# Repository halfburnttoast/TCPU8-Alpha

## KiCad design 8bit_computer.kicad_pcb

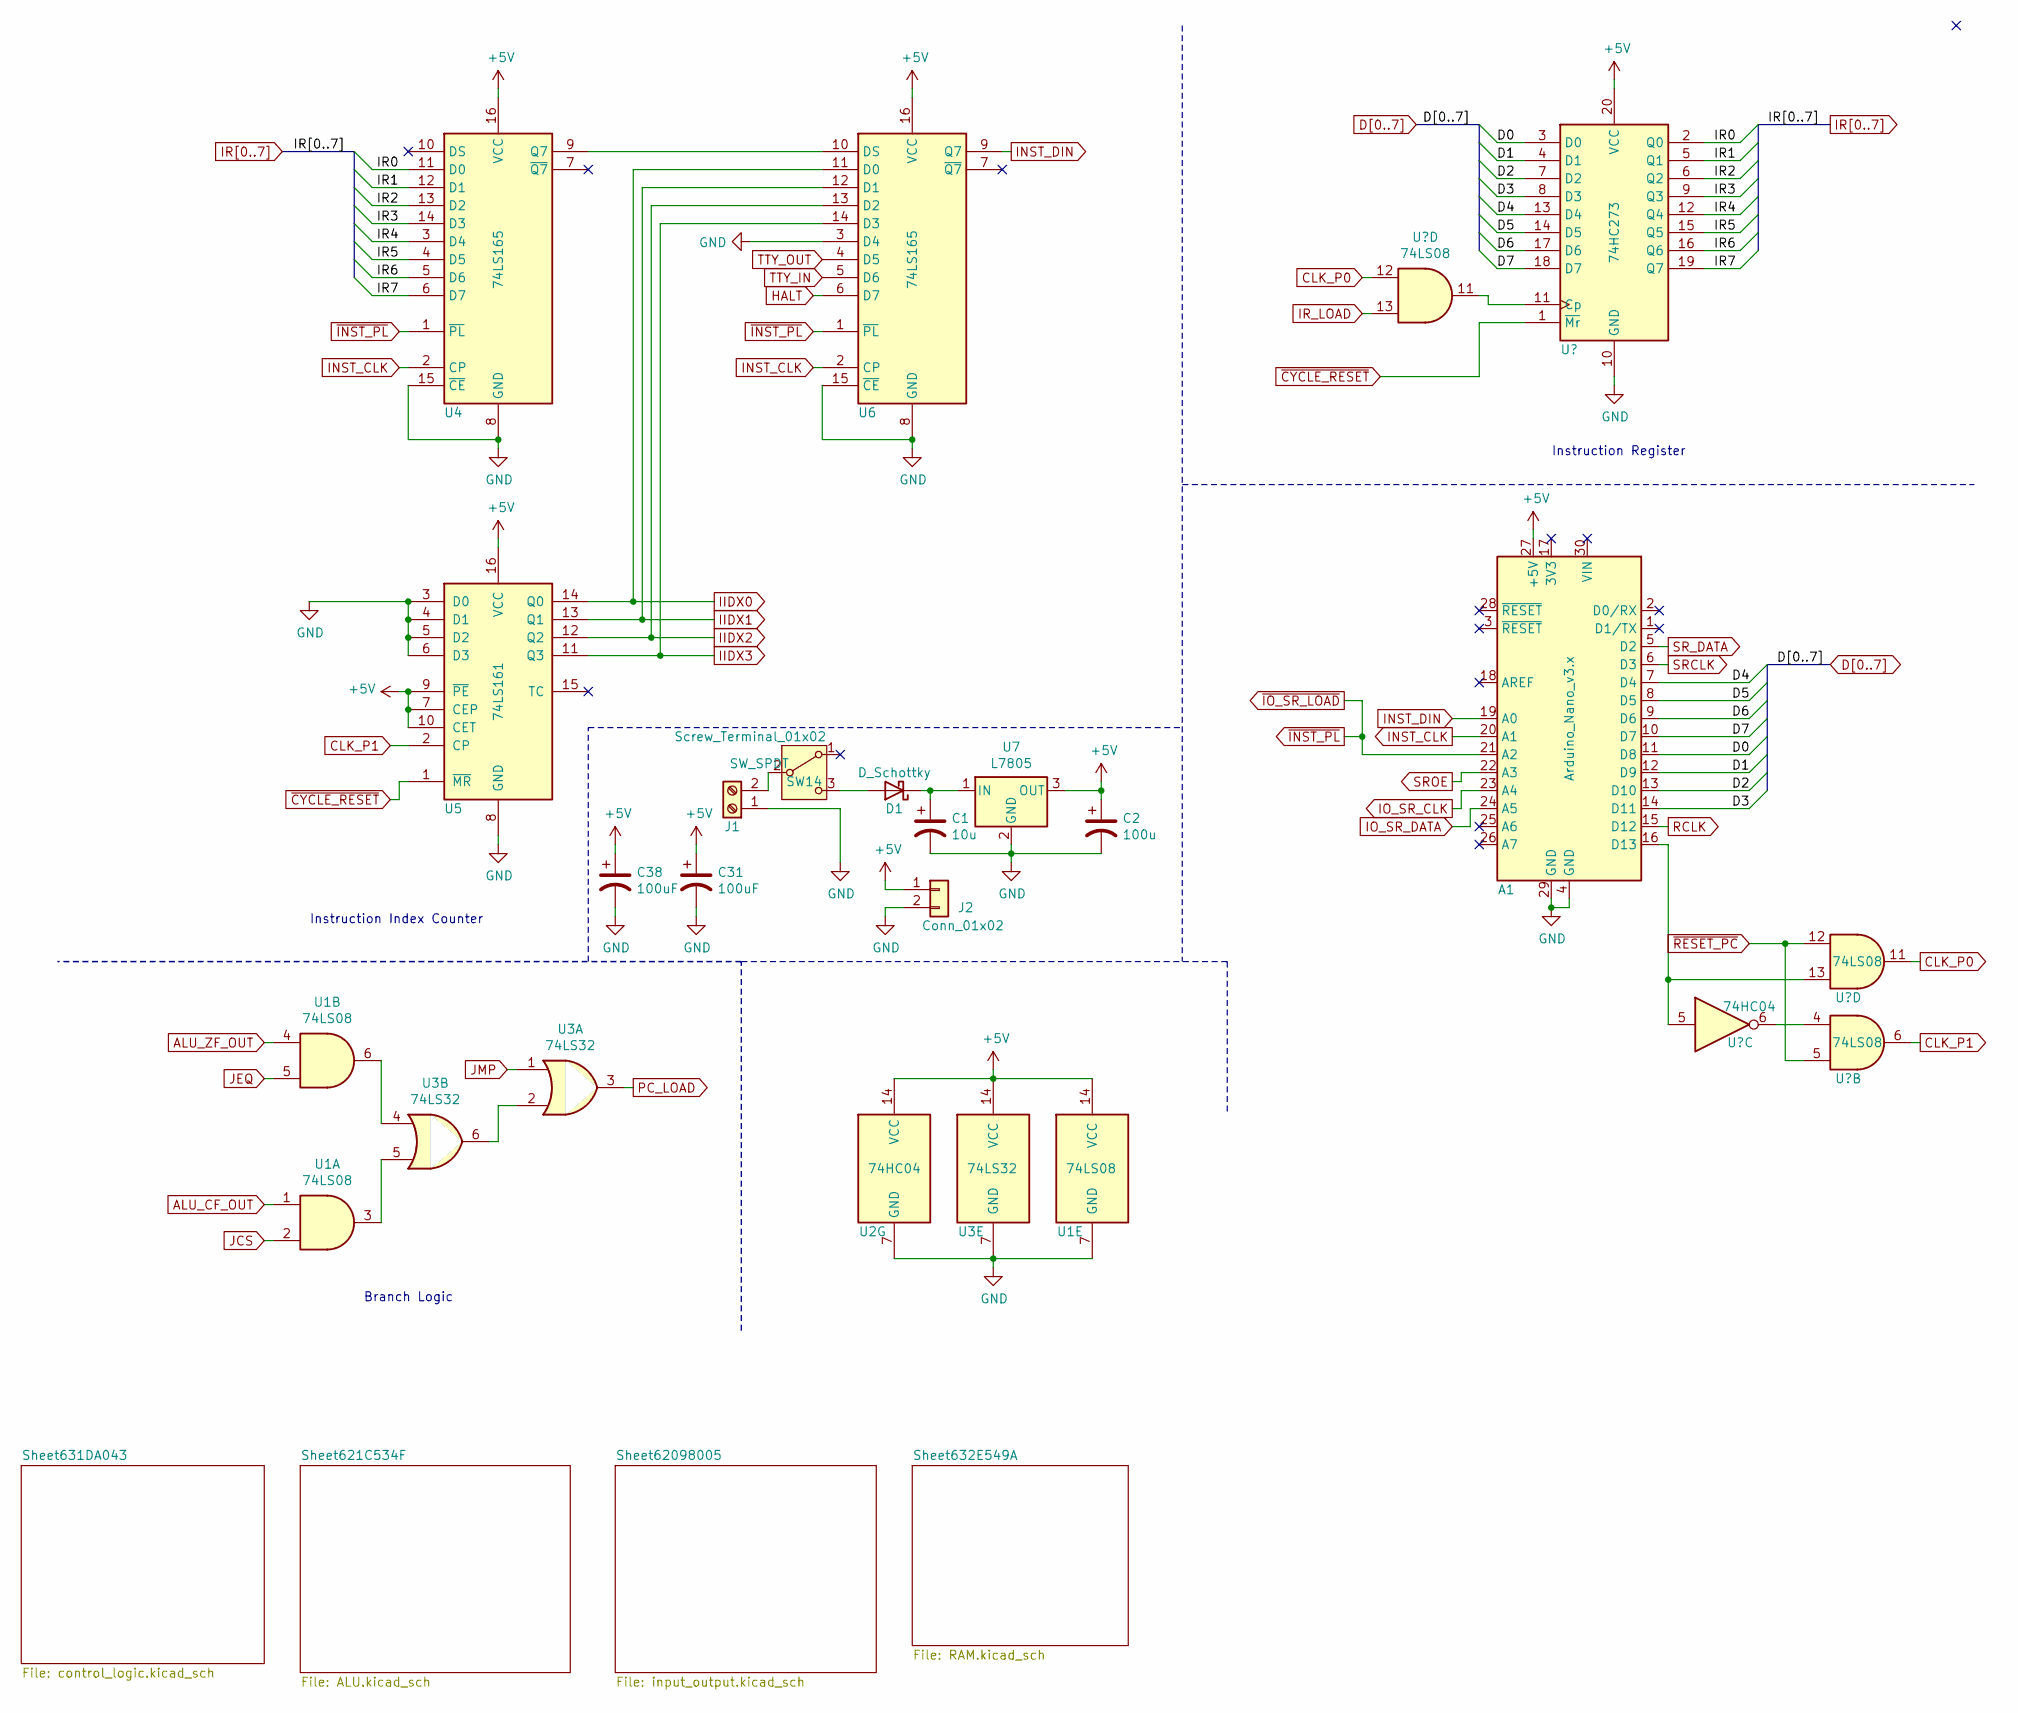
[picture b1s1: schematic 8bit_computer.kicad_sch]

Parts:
A1: Arduino_Nano_v3.x; Arduino_Nano
C1: 10u; CP_Radial_D4.0mm_P2.00mm
C2: 100u; CP_Radial_D4.0mm_P2.00mm
C31, C38: 100uF; CP_Radial_D4.0mm_P2.00mm
D1: D_Schottky; D_SOD-123
J1: Screw_Terminal_01x02; TerminalBlock_bornier-2_P5.08mm
J2: Conn_01x02; PinSocket_1x02_P2.54mm_Vertical
SW14: SW_SPDT; spdt_slide_switch
U1, U10: 74LS08; DIP-14_W7.62mm
U2: 74HC04; DIP-14_W7.62mm
U3: 74LS32; DIP-14_W7.62mm
U4, U6: 74LS165; DIP-16_W7.62mm
U5: 74LS161; DIP-16_W7.62mm
U7: L7805; TO-220F-3_Horizontal_TabDown
U8: 74HC273; DIP-20_W7.62mm

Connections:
+5V: A1.27 (+5V), C2.1, C31.1, C38.1, J2.1, U1.14 (VCC), U2.14 (VCC), U3.14 (VCC), U4.16 (VCC), U5.7 (CEP), U5.9 (~PE), U5.10 (CET), U5.16 (VCC), U6.16 (VCC), U7.3 (OUT), U8.20 (VCC); also elsewhere on the board
ALU_CF_OUT: U1.1; also elsewhere on the board
ALU_ZF_OUT: U1.4; also elsewhere on the board
CLK_P0: U1.12, U10.11; also elsewhere on the board
CLK_P1: U5.2 (CP), U10.6; also elsewhere on the board
D0: A1.11 (D8), U8.3 (D0); also elsewhere on the board
D1: A1.12 (D9), U8.4 (D1); also elsewhere on the board
D2: A1.13 (D10), U8.7 (D2); also elsewhere on the board
D3: A1.14 (D11), U8.8 (D3); also elsewhere on the board
D4: A1.7 (D4), U8.13 (D4); also elsewhere on the board
D5: A1.8 (D5), U8.14 (D5); also elsewhere on the board
D6: A1.9 (D6), U8.17 (D6); also elsewhere on the board
D7: A1.10 (D7), U8.18 (D7); also elsewhere on the board
GND: A1.4 (GND), A1.29 (GND), C1.2, C2.2, C31.2, C38.2, J1.1, J2.2, U1.7 (GND), U2.7 (GND), U3.7 (GND), U4.8 (GND), U4.15 (~CE), U5.3 (D0), U5.4 (D1), U5.5 (D2), U5.6 (D3), U5.8 (GND), U6.3 (D4), U6.8 (GND), U6.15 (~CE), U7.2 (GND), U8.10 (GND); also elsewhere on the board
HALT: U6.6 (D7); also elsewhere on the board
IIDX0: U5.14 (Q0), U6.11 (D0); also elsewhere on the board
IIDX1: U5.13 (Q1), U6.12 (D1); also elsewhere on the board
IIDX2: U5.12 (Q2), U6.13 (D2); also elsewhere on the board
IIDX3: U5.11 (Q3), U6.14 (D3); also elsewhere on the board
INST_CLK: A1.20 (A1), U4.2 (CP), U6.2 (CP)
INST_DIN: A1.19 (A0), U6.9 (Q7)
IO_SR_CLK: A1.23 (A4); also elsewhere on the board
IO_SR_DATA: A1.24 (A5); also elsewhere on the board
IR0: U4.11 (D0), U8.2 (Q0); also elsewhere on the board
IR1: U4.12 (D1), U8.5 (Q1); also elsewhere on the board
IR2: U4.13 (D2), U8.6 (Q2); also elsewhere on the board
IR3: U4.14 (D3), U8.9 (Q3); also elsewhere on the board
IR4: U4.3 (D4), U8.12 (Q4); also elsewhere on the board
IR5: U4.4 (D5), U8.15 (Q5); also elsewhere on the board
IR6: U4.5 (D6), U8.16 (Q6); also elsewhere on the board
IR7: U4.6 (D7), U8.19 (Q7); also elsewhere on the board
IR_LOAD: U1.13; also elsewhere on the board
JCS: U1.2; also elsewhere on the board
JEQ: U1.5; also elsewhere on the board
JMP: U3.1; also elsewhere on the board
unnamed: A1.16 (D13), U2.5, U10.13
unnamed: C1.1, D1.1 (K), U7.1 (IN)
unnamed: D1.2 (A), SW14.3 (C)
unnamed: J1.2, SW14.2 (B)
unnamed: U1.3, U3.5
unnamed: U1.6, U3.4
unnamed: U1.11, U8.11 (Cp)
unnamed: U3.2, U3.6
unnamed: U4.9 (Q7), U6.10 (DS)
unnamed: U2.6, U10.4
PC_LOAD: U3.3; also elsewhere on the board
RCLK: A1.15 (D12); also elsewhere on the board
SRCLK: A1.6 (D3); also elsewhere on the board
SROE: A1.22 (A3); also elsewhere on the board
SR_DATA: A1.5 (D2); also elsewhere on the board
TTY_IN: U6.5 (D6); also elsewhere on the board
TTY_OUT: U6.4 (D5); also elsewhere on the board
~CYCLE_RESET: U5.1 (~MR), U8.1 (~Mr); also elsewhere on the board
~INST_PL: A1.21 (A2), U4.1 (~PL), U6.1 (~PL); also elsewhere on the board
~RESET_PC: U10.5, U10.12; also elsewhere on the board

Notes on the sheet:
Instruction Register
Branch Logic
Instruction Index Counter

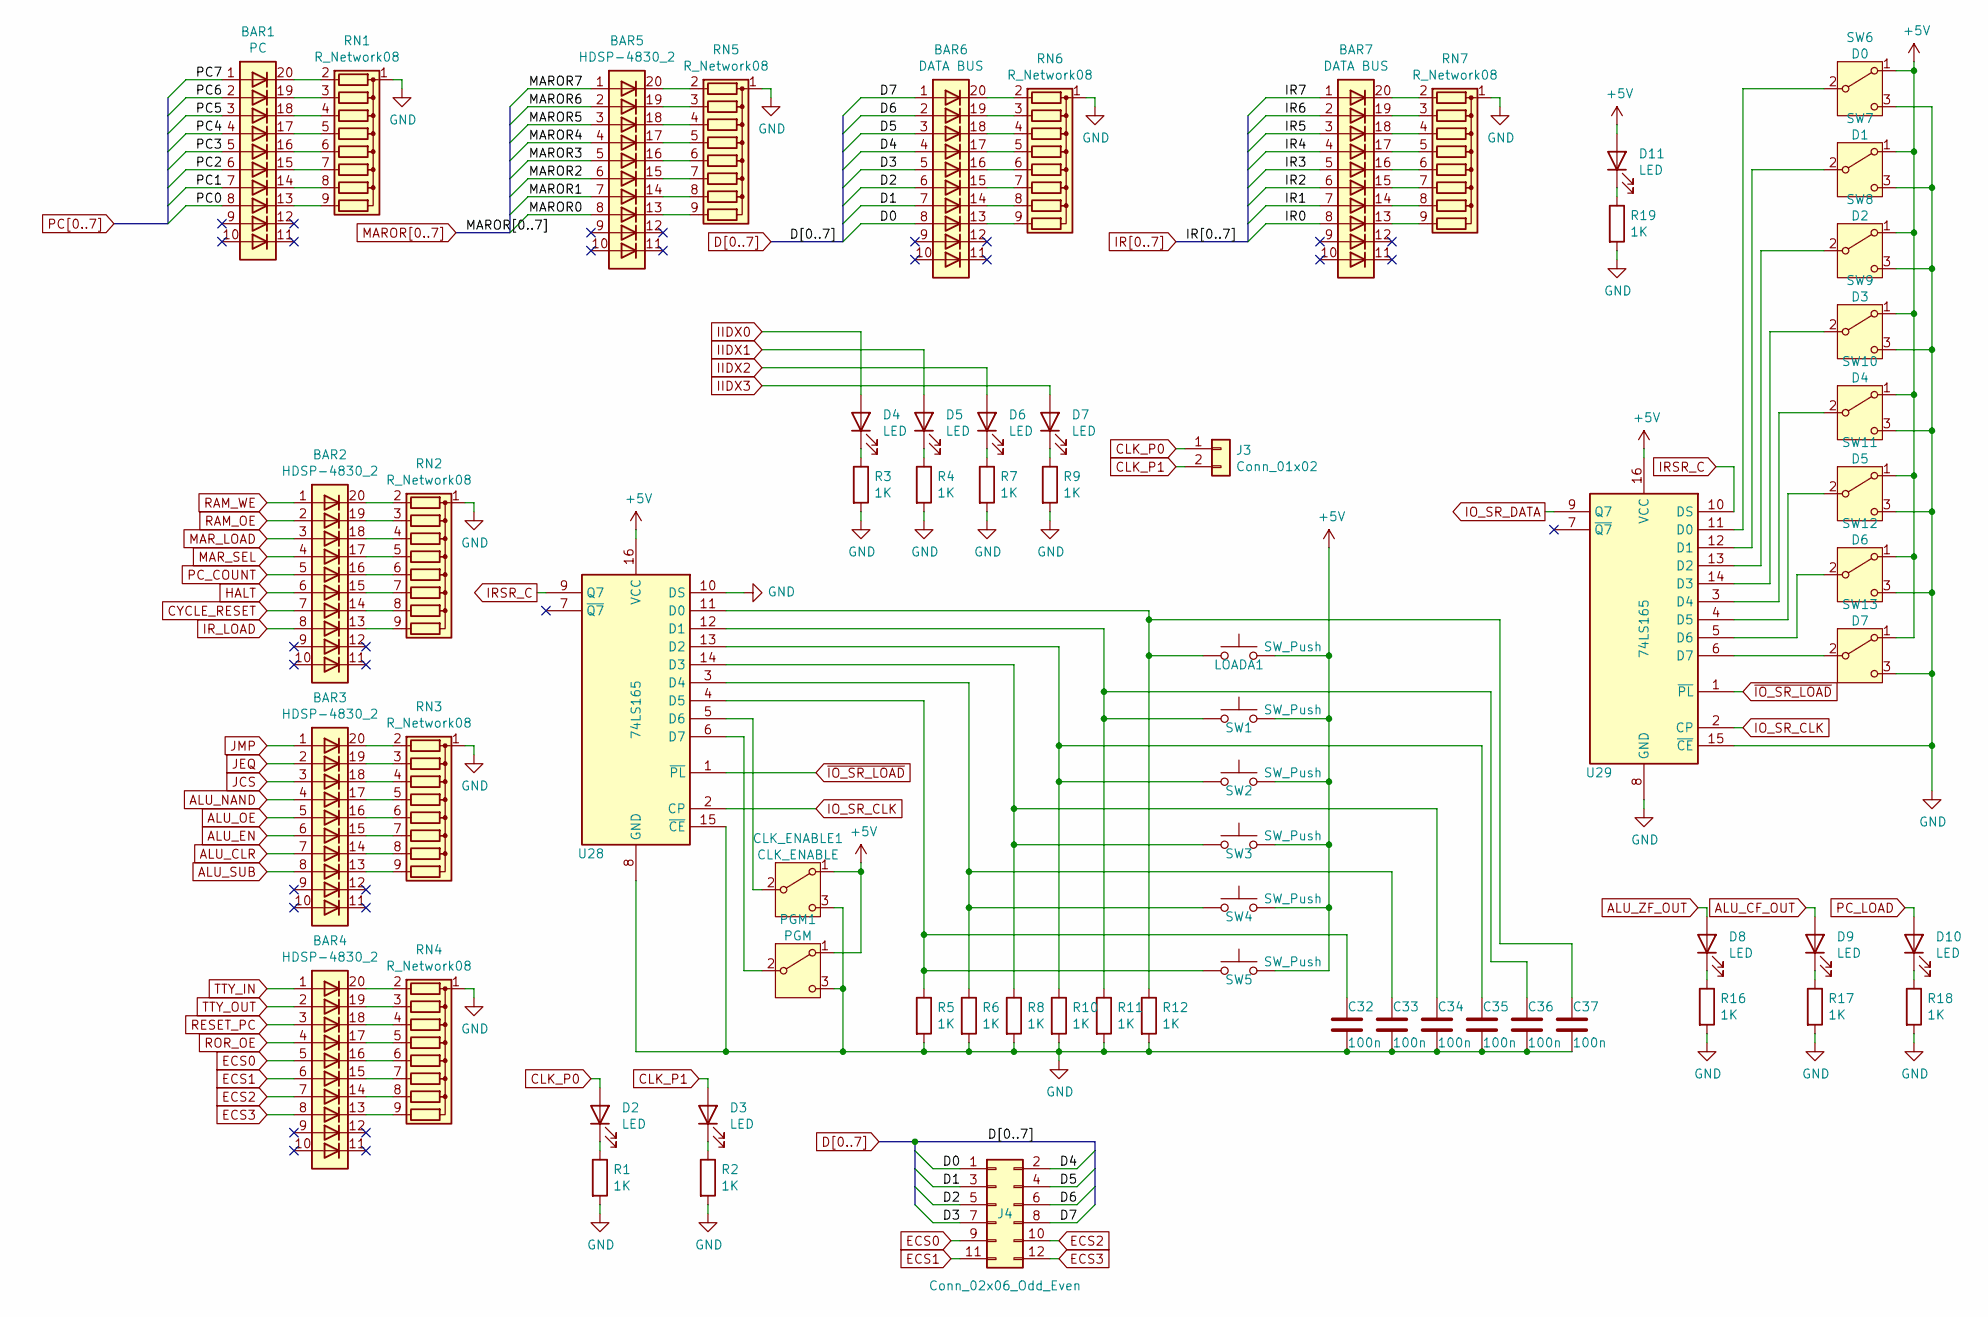
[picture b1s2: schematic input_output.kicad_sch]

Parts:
BAR1: PC; HDSP-4830
BAR2, BAR3, BAR4, BAR5: HDSP-4830_2; HDSP-4830
BAR6, BAR7: DATA BUS; HDSP-4830
C32, C33, C34, C35, C36, C37: 100n; C_1206_3216Metric_Pad1.42x1.75mm_HandSolder
CLK_ENABLE1: CLK_ENABLE; spdt_slide_switch
D2, D3: LED; LED_D5.0mm
D4, D5, D6, D7, D8, D9, D10, D11: LED; LED_D3.0mm
J3: Conn_01x02; PinSocket_1x02_P2.54mm_Vertical
J4: Conn_02x06_Odd_Even; PinSocket_2x06_P2.54mm_Vertical
LOADA1: SW_Push; SW_PUSH_6mm
PGM1: PGM; spdt_slide_switch
R1, R2, R3, R4, R5, R6, R7, R8, R9, R10, R11, R12, R19: 1K; R_Axial_DIN0207_L6.3mm_D2.5mm_P7.62mm_Horizontal
R16, R17, R18: 1K; R_1206_3216Metric_Pad1.42x1.75mm_HandSolder
RN1, RN2, RN3, RN4, RN5, RN6, RN7: R_Network08; R_Array_SIP9
SW1, SW2, SW3, SW4, SW5: SW_Push; SW_PUSH_6mm
SW6: D0; spdt_slide_switch
SW7: D1; spdt_slide_switch
SW8: D2; spdt_slide_switch
SW9: D3; spdt_slide_switch
SW10: D4; spdt_slide_switch
SW11: D5; spdt_slide_switch
SW12: D6; spdt_slide_switch
SW13: D7; spdt_slide_switch
U28, U29: 74LS165; DIP-16_W7.62mm

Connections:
+5V: CLK_ENABLE1.1 (A), D11.2 (A), LOADA1.2, PGM1.1 (A), SW1.2, SW2.2, SW3.2, SW4.2, SW5.2, SW6.1 (A), SW7.1 (A), SW8.1 (A), SW9.1 (A), SW10.1 (A), SW11.1 (A), SW12.1 (A), SW13.1 (A), U28.16 (VCC), U29.16 (VCC); also elsewhere on the board
ALU_CF_OUT: D9.2 (A); also elsewhere on the board
ALU_CLR: BAR3.7 (A); also elsewhere on the board
ALU_EN: BAR3.6 (A); also elsewhere on the board
ALU_NAND: BAR3.4 (A); also elsewhere on the board
ALU_OE: BAR3.5 (A); also elsewhere on the board
ALU_SUB: BAR3.8 (A); also elsewhere on the board
ALU_ZF_OUT: D8.2 (A); also elsewhere on the board
CLK_P0: D2.2 (A), J3.1; also elsewhere on the board
CLK_P1: D3.2 (A), J3.2; also elsewhere on the board
CYCLE_RESET: BAR2.7 (A); also elsewhere on the board
D0: BAR6.8 (A), J4.1; also elsewhere on the board
D1: BAR6.7 (A), J4.3; also elsewhere on the board
D2: BAR6.6 (A), J4.5; also elsewhere on the board
D3: BAR6.5 (A), J4.7; also elsewhere on the board
D4: BAR6.4 (A), J4.2; also elsewhere on the board
D5: BAR6.3 (A), J4.4; also elsewhere on the board
D6: BAR6.2 (A), J4.6; also elsewhere on the board
D7: BAR6.1 (A), J4.8; also elsewhere on the board
ECS0: BAR4.5 (A), J4.9; also elsewhere on the board
ECS1: BAR4.6 (A), J4.11; also elsewhere on the board
ECS2: BAR4.7 (A), J4.10; also elsewhere on the board
ECS3: BAR4.8 (A), J4.12; also elsewhere on the board
GND: C32.2, C33.2, C34.2, C35.2, C36.2, C37.2, CLK_ENABLE1.3 (C), PGM1.3 (C), R1.2, R2.2, R3.2, R4.2, R5.2, R6.2, R7.2, R8.2, R9.2, R10.2, R11.2, R12.2, R16.2, R17.2, R18.2, R19.2, RN1.1 (common), RN2.1 (common), RN3.1 (common), RN4.1 (common), RN5.1 (common), RN6.1 (common), RN7.1 (common), SW6.3 (C), SW7.3 (C), SW8.3 (C), SW9.3 (C), SW10.3 (C), SW11.3 (C), SW12.3 (C), SW13.3 (C), U28.8 (GND), U28.10 (DS), U28.15 (~CE), U29.8 (GND), U29.15 (~CE); also elsewhere on the board
HALT: BAR2.6 (A); also elsewhere on the board
IIDX0: D4.2 (A); also elsewhere on the board
IIDX1: D5.2 (A); also elsewhere on the board
IIDX2: D6.2 (A); also elsewhere on the board
IIDX3: D7.2 (A); also elsewhere on the board
IO_SR_CLK: U28.2 (CP), U29.2 (CP); also elsewhere on the board
IO_SR_DATA: U29.9 (Q7); also elsewhere on the board
IR0: BAR7.8 (A); also elsewhere on the board
IR1: BAR7.7 (A); also elsewhere on the board
IR2: BAR7.6 (A); also elsewhere on the board
IR3: BAR7.5 (A); also elsewhere on the board
IR4: BAR7.4 (A); also elsewhere on the board
IR5: BAR7.3 (A); also elsewhere on the board
IR6: BAR7.2 (A); also elsewhere on the board
IR7: BAR7.1 (A); also elsewhere on the board
IRSR_C: U28.9 (Q7), U29.10 (DS)
IR_LOAD: BAR2.8 (A); also elsewhere on the board
JCS: BAR3.3 (A); also elsewhere on the board
JEQ: BAR3.2 (A); also elsewhere on the board
JMP: BAR3.1 (A); also elsewhere on the board
MAROR0: BAR5.8 (A); also elsewhere on the board
MAROR1: BAR5.7 (A); also elsewhere on the board
MAROR2: BAR5.6 (A); also elsewhere on the board
MAROR3: BAR5.5 (A); also elsewhere on the board
MAROR4: BAR5.4 (A); also elsewhere on the board
MAROR5: BAR5.3 (A); also elsewhere on the board
MAROR6: BAR5.2 (A); also elsewhere on the board
MAROR7: BAR5.1 (A); also elsewhere on the board
MAR_LOAD: BAR2.3 (A); also elsewhere on the board
MAR_SEL: BAR2.4 (A); also elsewhere on the board
unnamed: BAR1.13 (K), RN1.9 (R8)
unnamed: BAR1.14 (K), RN1.8 (R7)
unnamed: BAR1.15 (K), RN1.7 (R6)
unnamed: BAR1.16 (K), RN1.6 (R5)
unnamed: BAR1.17 (K), RN1.5 (R4)
unnamed: BAR1.18 (K), RN1.4 (R3)
unnamed: BAR1.19 (K), RN1.3 (R2)
unnamed: BAR1.20 (K), RN1.2 (R1)
unnamed: BAR2.13 (K), RN2.9 (R8)
unnamed: BAR2.14 (K), RN2.8 (R7)
unnamed: BAR2.15 (K), RN2.7 (R6)
unnamed: BAR2.16 (K), RN2.6 (R5)
unnamed: BAR2.17 (K), RN2.5 (R4)
unnamed: BAR2.18 (K), RN2.4 (R3)
unnamed: BAR2.19 (K), RN2.3 (R2)
unnamed: BAR2.20 (K), RN2.2 (R1)
unnamed: BAR3.13 (K), RN3.9 (R8)
unnamed: BAR3.14 (K), RN3.8 (R7)
unnamed: BAR3.15 (K), RN3.7 (R6)
unnamed: BAR3.16 (K), RN3.6 (R5)
unnamed: BAR3.17 (K), RN3.5 (R4)
unnamed: BAR3.18 (K), RN3.4 (R3)
unnamed: BAR3.19 (K), RN3.3 (R2)
unnamed: BAR3.20 (K), RN3.2 (R1)
unnamed: BAR4.13 (K), RN4.9 (R8)
unnamed: BAR4.14 (K), RN4.8 (R7)
unnamed: BAR4.15 (K), RN4.7 (R6)
unnamed: BAR4.16 (K), RN4.6 (R5)
unnamed: BAR4.17 (K), RN4.5 (R4)
unnamed: BAR4.18 (K), RN4.4 (R3)
unnamed: BAR4.19 (K), RN4.3 (R2)
unnamed: BAR4.20 (K), RN4.2 (R1)
unnamed: BAR5.13 (K), RN5.9 (R8)
unnamed: BAR5.14 (K), RN5.8 (R7)
unnamed: BAR5.15 (K), RN5.7 (R6)
unnamed: BAR5.16 (K), RN5.6 (R5)
unnamed: BAR5.17 (K), RN5.5 (R4)
unnamed: BAR5.18 (K), RN5.4 (R3)
unnamed: BAR5.19 (K), RN5.3 (R2)
unnamed: BAR5.20 (K), RN5.2 (R1)
unnamed: BAR6.13 (K), RN6.9 (R8)
unnamed: BAR6.14 (K), RN6.8 (R7)
unnamed: BAR6.15 (K), RN6.7 (R6)
unnamed: BAR6.16 (K), RN6.6 (R5)
unnamed: BAR6.17 (K), RN6.5 (R4)
unnamed: BAR6.18 (K), RN6.4 (R3)
unnamed: BAR6.19 (K), RN6.3 (R2)
unnamed: BAR6.20 (K), RN6.2 (R1)
unnamed: BAR7.13 (K), RN7.9 (R8)
unnamed: BAR7.14 (K), RN7.8 (R7)
unnamed: BAR7.15 (K), RN7.7 (R6)
unnamed: BAR7.16 (K), RN7.6 (R5)
unnamed: BAR7.17 (K), RN7.5 (R4)
unnamed: BAR7.18 (K), RN7.4 (R3)
unnamed: BAR7.19 (K), RN7.3 (R2)
unnamed: BAR7.20 (K), RN7.2 (R1)
unnamed: C32.1, R5.1, SW5.1, U28.4 (D5)
unnamed: C33.1, R6.1, SW4.1, U28.3 (D4)
unnamed: C34.1, R8.1, SW3.1, U28.14 (D3)
unnamed: C35.1, R10.1, SW2.1, U28.13 (D2)
unnamed: C36.1, R11.1, SW1.1, U28.12 (D1)
unnamed: C37.1, LOADA1.1, R12.1, U28.11 (D0)
unnamed: CLK_ENABLE1.2 (B), U28.5 (D6)
unnamed: D2.1 (K), R1.1
unnamed: D3.1 (K), R2.1
unnamed: D4.1 (K), R3.1
unnamed: D5.1 (K), R4.1
unnamed: D6.1 (K), R7.1
unnamed: D7.1 (K), R9.1
unnamed: D8.1 (K), R16.1
unnamed: D9.1 (K), R17.1
unnamed: D10.1 (K), R18.1
unnamed: D11.1 (K), R19.1
unnamed: PGM1.2 (B), U28.6 (D7)
unnamed: SW6.2 (B), U29.11 (D0)
unnamed: SW7.2 (B), U29.12 (D1)
unnamed: SW8.2 (B), U29.13 (D2)
unnamed: SW9.2 (B), U29.14 (D3)
unnamed: SW10.2 (B), U29.3 (D4)
unnamed: SW11.2 (B), U29.4 (D5)
unnamed: SW12.2 (B), U29.5 (D6)
unnamed: SW13.2 (B), U29.6 (D7)
PC0: BAR1.8 (A); also elsewhere on the board
PC1: BAR1.7 (A); also elsewhere on the board
PC2: BAR1.6 (A); also elsewhere on the board
PC3: BAR1.5 (A); also elsewhere on the board
PC4: BAR1.4 (A); also elsewhere on the board
PC5: BAR1.3 (A); also elsewhere on the board
PC6: BAR1.2 (A); also elsewhere on the board
PC7: BAR1.1 (A); also elsewhere on the board
PC_COUNT: BAR2.5 (A); also elsewhere on the board
PC_LOAD: D10.2 (A); also elsewhere on the board
RAM_OE: BAR2.2 (A); also elsewhere on the board
RAM_WE: BAR2.1 (A); also elsewhere on the board
RESET_PC: BAR4.3 (A); also elsewhere on the board
ROR_OE: BAR4.4 (A); also elsewhere on the board
TTY_IN: BAR4.1 (A); also elsewhere on the board
TTY_OUT: BAR4.2 (A); also elsewhere on the board
~INST_PL: U28.1 (~PL), U29.1 (~PL); also elsewhere on the board

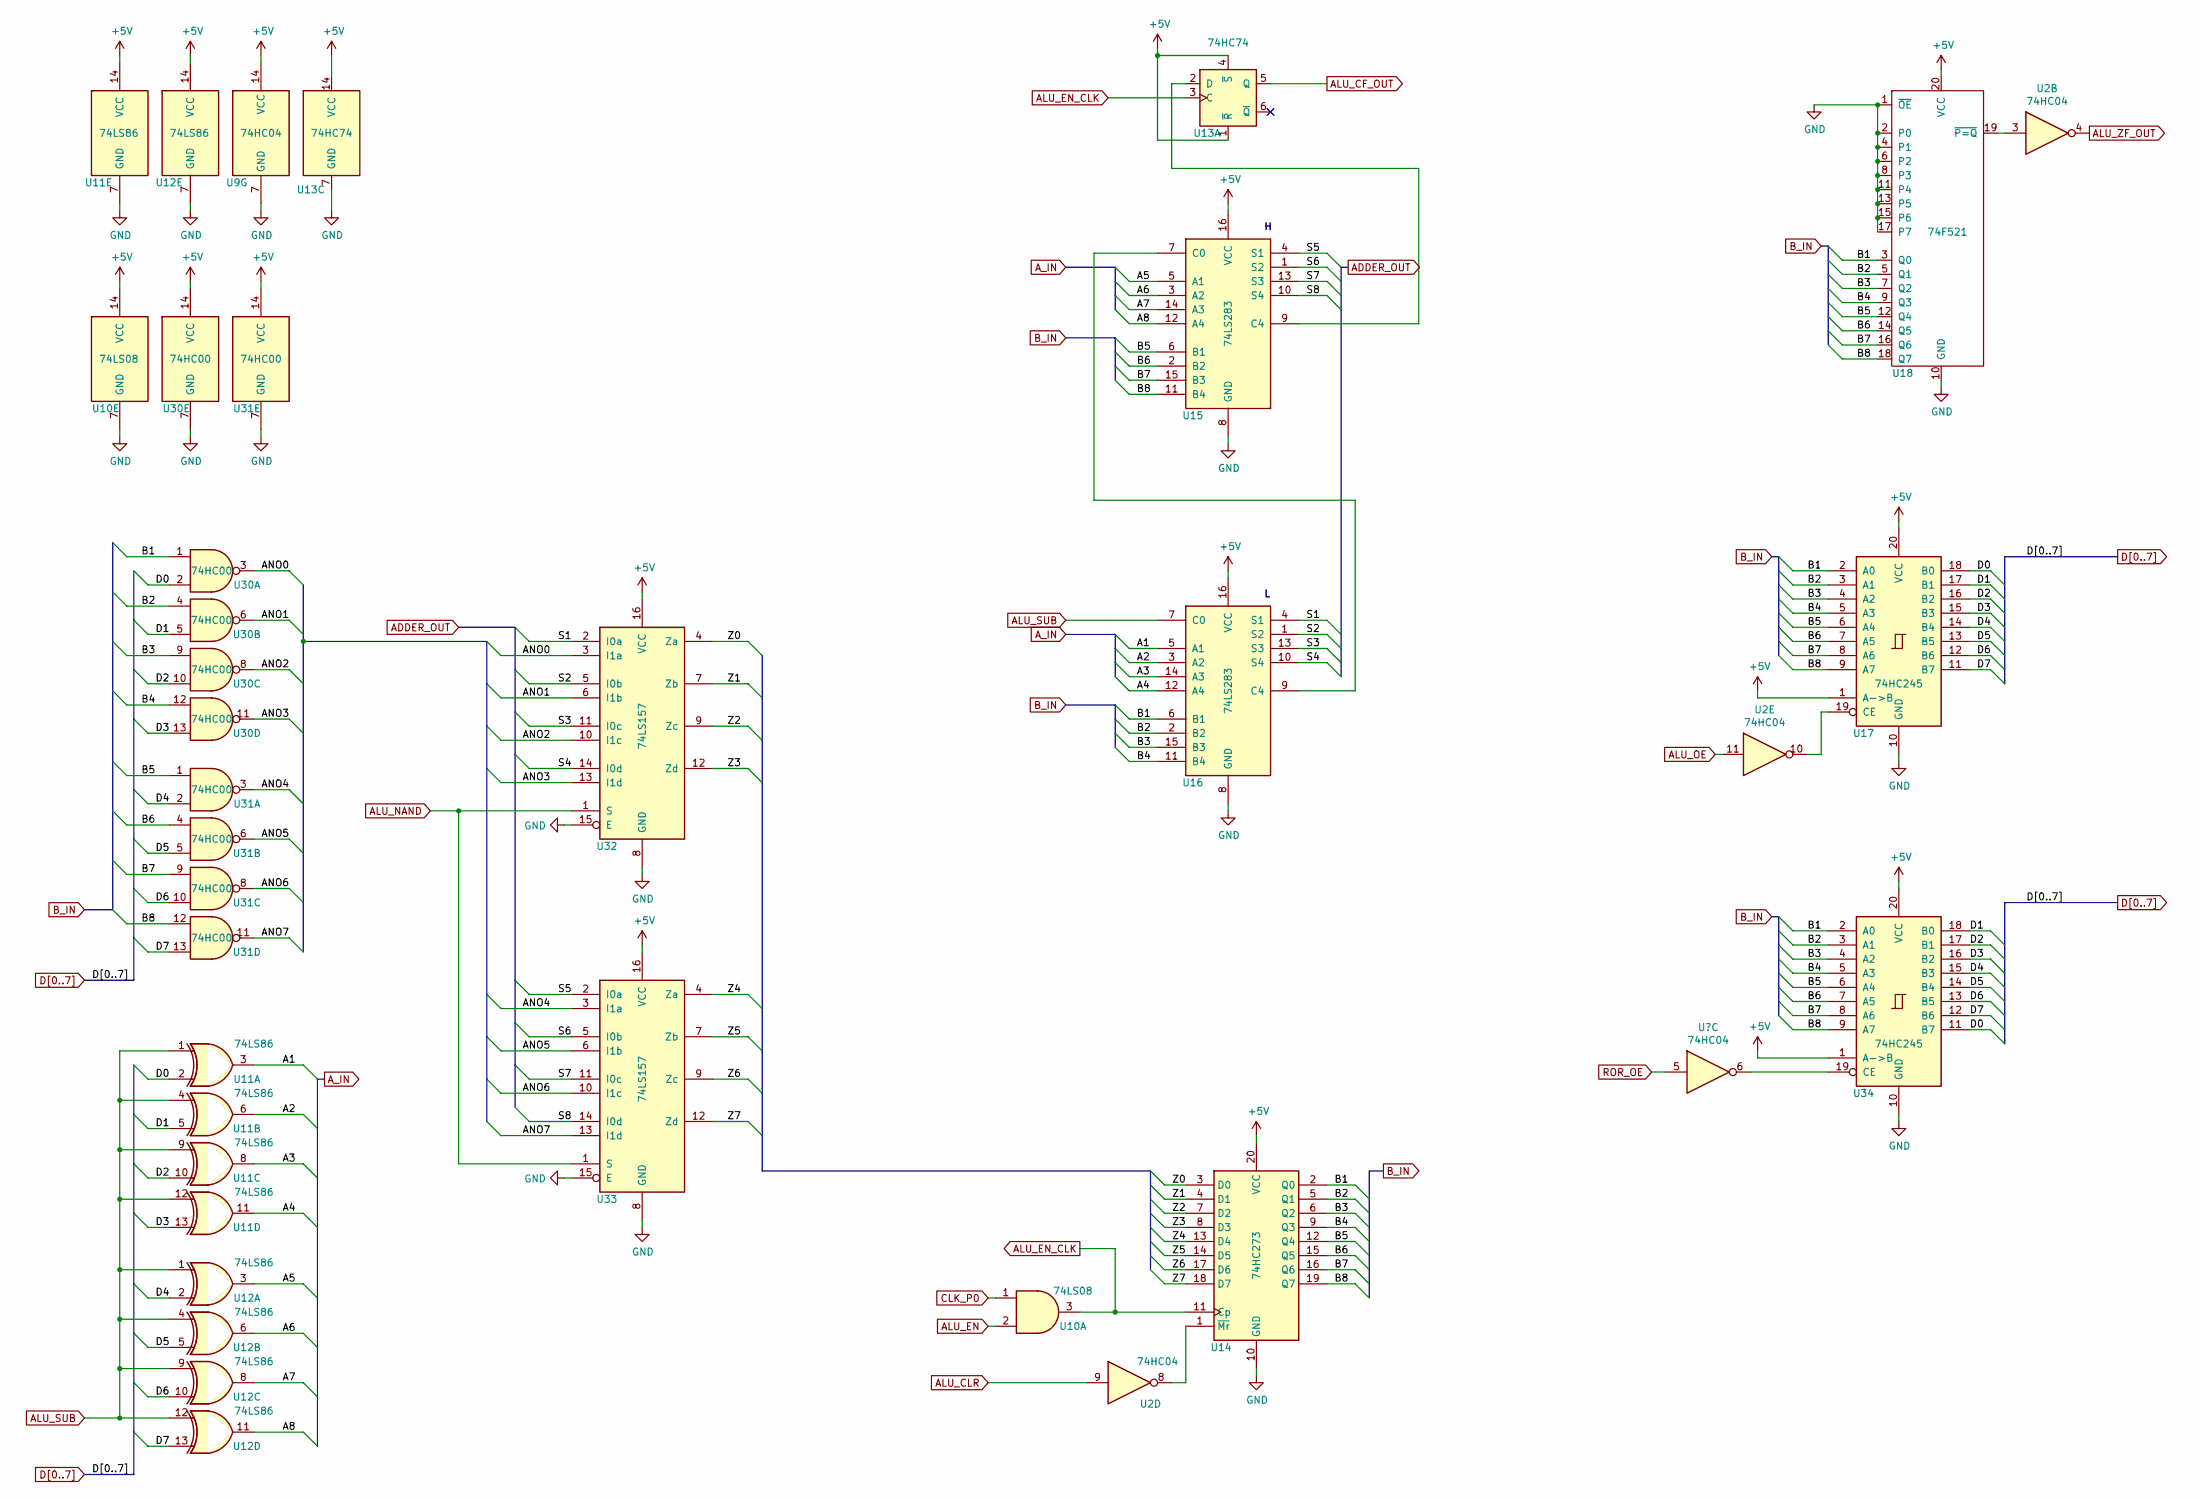
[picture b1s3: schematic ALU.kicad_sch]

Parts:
U2, U9: 74HC04; DIP-14_W7.62mm
U10: 74LS08; DIP-14_W7.62mm
U11, U12: 74LS86; DIP-14_W7.62mm
U13: 74HC74; DIP-14_W7.62mm
U14: 74HC273; DIP-20_W7.62mm
U15, U16: 74LS283; DIP-16_W7.62mm
U17, U34: 74HC245; DIP-20_W7.62mm
U18: 74F521; DIP-20_W7.62mm
U30, U31: 74HC00; DIP-14_W7.62mm
U32, U33: 74LS157; DIP-16_W7.62mm

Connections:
+5V: U9.14 (VCC), U10.14 (VCC), U11.14 (VCC), U12.14 (VCC), U13.1 (~R), U13.4 (~S), U13.14 (VCC), U14.20 (VCC), U15.16 (VCC), U16.16 (VCC), U17.1 (A->B), U17.20 (VCC), U18.20 (VCC), U30.14 (VCC), U31.14 (VCC), U32.16 (VCC), U33.16 (VCC), U34.1 (A->B), U34.20 (VCC); also elsewhere on the board
/Sheet621C534F/A1: U11.3, U16.5 (A1)
/Sheet621C534F/A2: U11.6, U16.3 (A2)
/Sheet621C534F/A3: U11.8, U16.14 (A3)
/Sheet621C534F/A4: U11.11, U16.12 (A4)
/Sheet621C534F/A5: U12.3, U15.5 (A1)
/Sheet621C534F/A6: U12.6, U15.3 (A2)
/Sheet621C534F/A7: U12.8, U15.14 (A3)
/Sheet621C534F/A8: U12.11, U15.12 (A4)
/Sheet621C534F/ANO0: U30.3, U32.3 (I1a)
/Sheet621C534F/ANO1: U30.6, U32.6 (I1b)
/Sheet621C534F/ANO2: U30.8, U32.10 (I1c)
/Sheet621C534F/ANO3: U30.11, U32.13 (I1d)
/Sheet621C534F/ANO4: U31.3, U33.3 (I1a)
/Sheet621C534F/ANO5: U31.6, U33.6 (I1b)
/Sheet621C534F/ANO6: U31.8, U33.10 (I1c)
/Sheet621C534F/ANO7: U31.11, U33.13 (I1d)
/Sheet621C534F/B1: U14.2 (Q0), U16.6 (B1), U17.2 (A0), U18.3 (Q0), U30.1, U34.2 (A0)
/Sheet621C534F/B2: U14.5 (Q1), U16.2 (B2), U17.3 (A1), U18.5 (Q1), U30.4, U34.3 (A1)
/Sheet621C534F/B3: U14.6 (Q2), U16.15 (B3), U17.4 (A2), U18.7 (Q2), U30.9, U34.4 (A2)
/Sheet621C534F/B4: U14.9 (Q3), U16.11 (B4), U17.5 (A3), U18.9 (Q3), U30.12, U34.5 (A3)
/Sheet621C534F/B5: U14.12 (Q4), U15.6 (B1), U17.6 (A4), U18.12 (Q4), U31.1, U34.6 (A4)
/Sheet621C534F/B6: U14.15 (Q5), U15.2 (B2), U17.7 (A5), U18.14 (Q5), U31.4, U34.7 (A5)
/Sheet621C534F/B7: U14.16 (Q6), U15.15 (B3), U17.8 (A6), U18.16 (Q6), U31.9, U34.8 (A6)
/Sheet621C534F/B8: U14.19 (Q7), U15.11 (B4), U17.9 (A7), U18.18 (Q7), U31.12, U34.9 (A7)
/Sheet621C534F/S1: U16.4 (S1), U32.2 (I0a)
/Sheet621C534F/S2: U16.1 (S2), U32.5 (I0b)
/Sheet621C534F/S3: U16.13 (S3), U32.11 (I0c)
/Sheet621C534F/S4: U16.10 (S4), U32.14 (I0d)
/Sheet621C534F/S5: U15.4 (S1), U33.2 (I0a)
/Sheet621C534F/S6: U15.1 (S2), U33.5 (I0b)
/Sheet621C534F/S7: U15.13 (S3), U33.11 (I0c)
/Sheet621C534F/S8: U15.10 (S4), U33.14 (I0d)
/Sheet621C534F/Z0: U14.3 (D0), U32.4 (Za)
/Sheet621C534F/Z1: U14.4 (D1), U32.7 (Zb)
/Sheet621C534F/Z2: U14.7 (D2), U32.9 (Zc)
/Sheet621C534F/Z3: U14.8 (D3), U32.12 (Zd)
/Sheet621C534F/Z4: U14.13 (D4), U33.4 (Za)
/Sheet621C534F/Z5: U14.14 (D5), U33.7 (Zb)
/Sheet621C534F/Z6: U14.17 (D6), U33.9 (Zc)
/Sheet621C534F/Z7: U14.18 (D7), U33.12 (Zd)
ALU_CF_OUT: U13.5 (Q); also elsewhere on the board
ALU_CLR: U2.9; also elsewhere on the board
ALU_EN: U10.2; also elsewhere on the board
ALU_EN_CLK: U10.3, U13.3 (C), U14.11 (Cp)
ALU_NAND: U32.1 (S), U33.1 (S); also elsewhere on the board
ALU_OE: U2.11; also elsewhere on the board
ALU_SUB: U11.1, U11.4, U11.9, U11.12, U12.1, U12.4, U12.9, U12.12, U16.7 (C0); also elsewhere on the board
ALU_ZF_OUT: U2.4; also elsewhere on the board
CLK_P0: U10.1; also elsewhere on the board
D0: U11.2, U17.18 (B0), U30.2, U34.11 (B7); also elsewhere on the board
D1: U11.5, U17.17 (B1), U30.5, U34.18 (B0); also elsewhere on the board
D2: U11.10, U17.16 (B2), U30.10, U34.17 (B1); also elsewhere on the board
D3: U11.13, U17.15 (B3), U30.13, U34.16 (B2); also elsewhere on the board
D4: U12.2, U17.14 (B4), U31.2, U34.15 (B3); also elsewhere on the board
D5: U12.5, U17.13 (B5), U31.5, U34.14 (B4); also elsewhere on the board
D6: U12.10, U17.12 (B6), U31.10, U34.13 (B5); also elsewhere on the board
D7: U12.13, U17.11 (B7), U31.13, U34.12 (B6); also elsewhere on the board
GND: U9.7 (GND), U10.7 (GND), U11.7 (GND), U12.7 (GND), U13.7 (GND), U14.10 (GND), U15.8 (GND), U16.8 (GND), U17.10 (GND), U18.1 (~OE), U18.2 (P0), U18.4 (P1), U18.6 (P2), U18.8 (P3), U18.10 (GND), U18.11 (P4), U18.13 (P5), U18.15 (P6), U18.17 (P7), U30.7 (GND), U31.7 (GND), U32.8 (GND), U32.15 (E), U33.8 (GND), U33.15 (E), U34.10 (GND); also elsewhere on the board
unnamed: U13.2 (D), U15.9 (C4)
unnamed: U2.8, U14.1 (~Mr)
unnamed: U15.7 (C0), U16.9 (C4)
unnamed: U2.10, U17.19 (CE)
unnamed: U2.3, U18.19 (~P=Q)
unnamed: U9.6, U34.19 (CE)
ROR_OE: U9.5; also elsewhere on the board

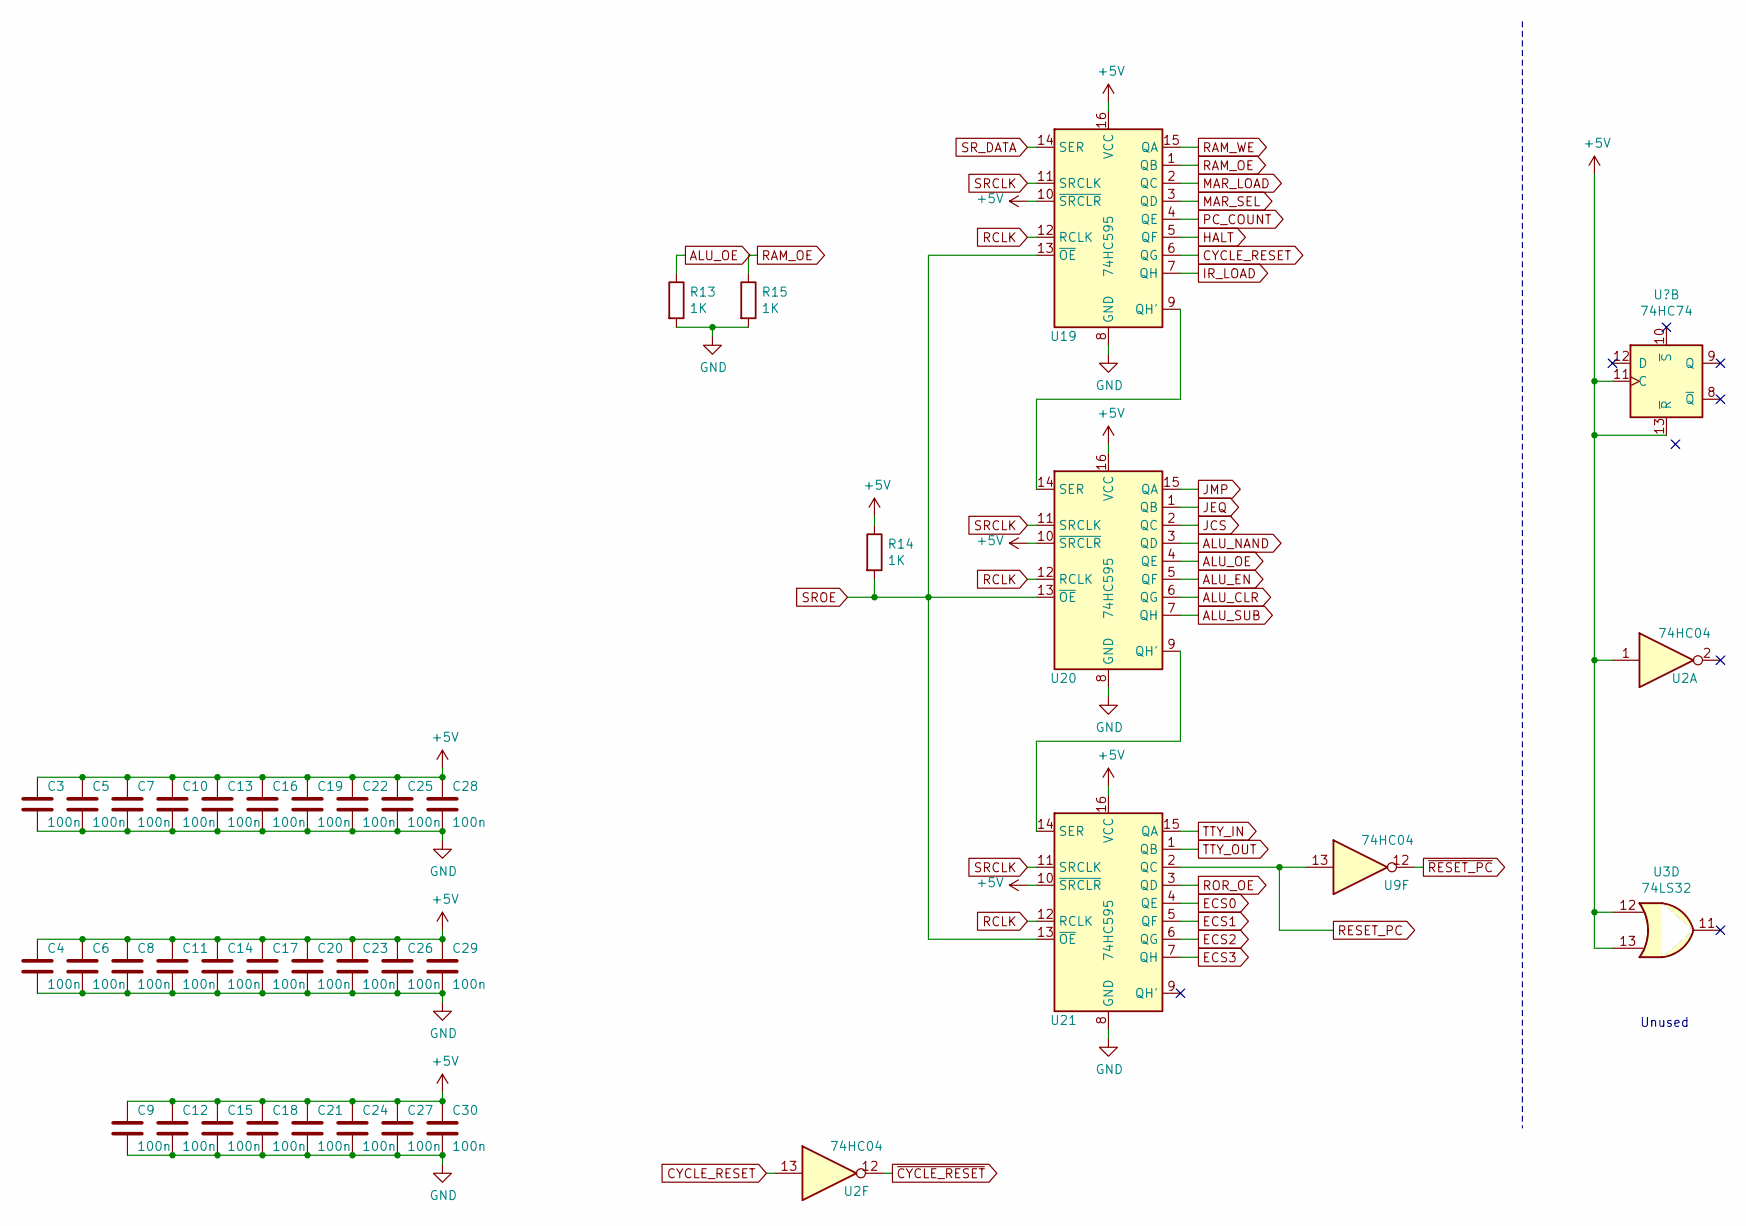
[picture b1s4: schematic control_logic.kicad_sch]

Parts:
C3, C4, C5, C6, C7, C8, C9, C10, C11, C12, C13, C14, C15, C16, C17, C18, C19, C20, C21, C22, C23, C24, C25, C26, C27, C28, C29, C30: 100n; C_Disc_D4.3mm_W1.9mm_P5.00mm
R13, R15: 1K; R_1206_3216Metric_Pad1.42x1.75mm_HandSolder
R14: 1K; R_Axial_DIN0207_L6.3mm_D2.5mm_P7.62mm_Horizontal
U2, U9: 74HC04; DIP-14_W7.62mm
U3: 74LS32; DIP-14_W7.62mm
U13: 74HC74; DIP-14_W7.62mm
U19, U20, U21: 74HC595; DIP-16_W7.62mm

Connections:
+5V: C3.1, C4.1, C5.1, C6.1, C7.1, C8.1, C9.1, C10.1, C11.1, C12.1, C13.1, C14.1, C15.1, C16.1, C17.1, C18.1, C19.1, C20.1, C21.1, C22.1, C23.1, C24.1, C25.1, C26.1, C27.1, C28.1, C29.1, C30.1, R14.1, U2.1, U3.12, U3.13, U13.11 (C), U13.13 (~R), U19.10 (~SRCLR), U19.16 (VCC), U20.10 (~SRCLR), U20.16 (VCC), U21.10 (~SRCLR), U21.16 (VCC); also elsewhere on the board
ALU_CLR: U20.6 (QG); also elsewhere on the board
ALU_EN: U20.5 (QF); also elsewhere on the board
ALU_NAND: U20.3 (QD); also elsewhere on the board
ALU_OE: R13.1, U20.4 (QE); also elsewhere on the board
ALU_SUB: U20.7 (QH); also elsewhere on the board
CYCLE_RESET: U2.13, U19.6 (QG); also elsewhere on the board
ECS0: U21.4 (QE); also elsewhere on the board
ECS1: U21.5 (QF); also elsewhere on the board
ECS2: U21.6 (QG); also elsewhere on the board
ECS3: U21.7 (QH); also elsewhere on the board
GND: C3.2, C4.2, C5.2, C6.2, C7.2, C8.2, C9.2, C10.2, C11.2, C12.2, C13.2, C14.2, C15.2, C16.2, C17.2, C18.2, C19.2, C20.2, C21.2, C22.2, C23.2, C24.2, C25.2, C26.2, C27.2, C28.2, C29.2, C30.2, R13.2, R15.2, U19.8 (GND), U20.8 (GND), U21.8 (GND); also elsewhere on the board
HALT: U19.5 (QF); also elsewhere on the board
IR_LOAD: U19.7 (QH); also elsewhere on the board
JCS: U20.2 (QC); also elsewhere on the board
JEQ: U20.1 (QB); also elsewhere on the board
JMP: U20.15 (QA); also elsewhere on the board
MAR_LOAD: U19.2 (QC); also elsewhere on the board
MAR_SEL: U19.3 (QD); also elsewhere on the board
unnamed: U19.9 (QH'), U20.14 (SER)
unnamed: U20.9 (QH'), U21.14 (SER)
PC_COUNT: U19.4 (QE); also elsewhere on the board
RAM_OE: R15.1, U19.1 (QB); also elsewhere on the board
RAM_WE: U19.15 (QA); also elsewhere on the board
RCLK: U19.12 (RCLK), U20.12 (RCLK), U21.12 (RCLK); also elsewhere on the board
RESET_PC: U9.13, U21.2 (QC); also elsewhere on the board
ROR_OE: U21.3 (QD); also elsewhere on the board
SRCLK: U19.11 (SRCLK), U20.11 (SRCLK), U21.11 (SRCLK); also elsewhere on the board
SROE: R14.2, U19.13 (~OE), U20.13 (~OE), U21.13 (~OE); also elsewhere on the board
SR_DATA: U19.14 (SER); also elsewhere on the board
TTY_IN: U21.15 (QA); also elsewhere on the board
TTY_OUT: U21.1 (QB); also elsewhere on the board
~CYCLE_RESET: U2.12; also elsewhere on the board
~RESET_PC: U9.12; also elsewhere on the board

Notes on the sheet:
Unused
